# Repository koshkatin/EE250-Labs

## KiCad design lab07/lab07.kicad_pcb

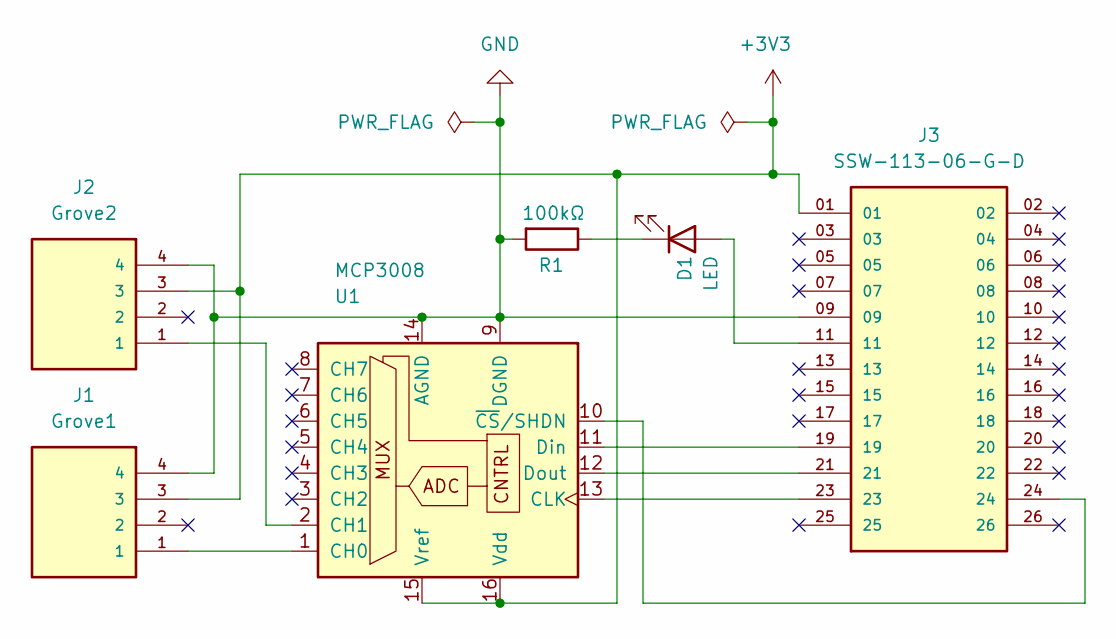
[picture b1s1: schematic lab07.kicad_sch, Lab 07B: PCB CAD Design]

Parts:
D1: LED; LED_D3.0mm
J1: Grove1; SEEED_110990030; PARTREV A
J2: Grove2; SEEED_110990030; PARTREV A
J3: SSW-113-06-G-D; SAMTEC_SSW-113-06-G-D; PARTREV R
R1: 100kΩ; R_Axial_DIN0207_L6.3mm_D2.5mm_P7.62mm_Horizontal
U1: MCP3008; DIP16-2.54-19.2X7.62MM

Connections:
+3V3: J1.3, J2.3, J3.01, U1.15 (Vref), U1.16 (Vdd)
GND: J1.4, J2.4, J3.09, R1.2, U1.9 (DGND), U1.14 (AGND)
unnamed: D1.2 (A), J3.11
unnamed: D1.1 (K), R1.1
unnamed: J1.1, U1.1 (CH0)
unnamed: J2.1, U1.2 (CH1)
unnamed: J3.23, U1.13 (CLK)
unnamed: J3.19, U1.11 (Din)
unnamed: J3.21, U1.12 (Dout)
unnamed: J3.24, U1.10 (~CS/SHDN)

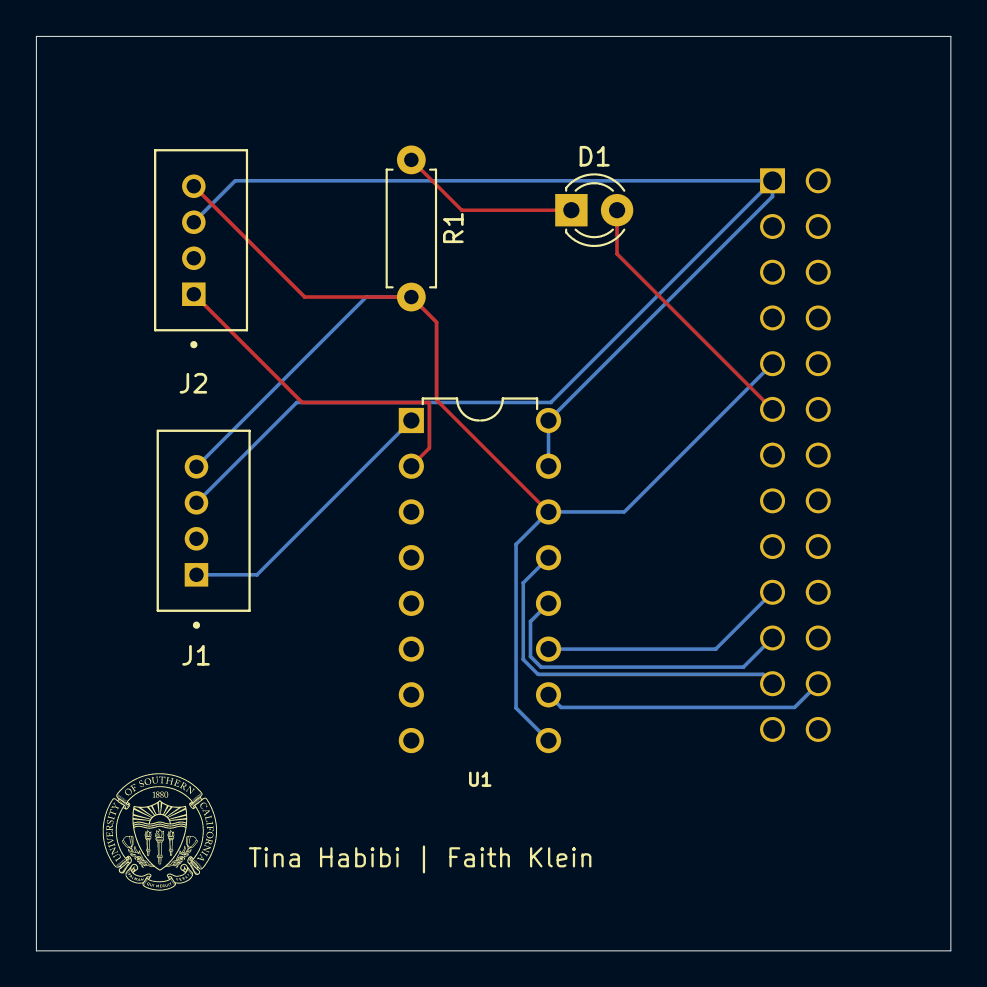
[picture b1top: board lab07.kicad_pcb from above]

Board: 2 copper layers, 50.8 x 50.8 mm, 6 parts (1 on the bottom side), 10 nets.

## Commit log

2025-02-04 Added
2025-02-08 lab3 server.py docstrings
2025-02-17 lab4 added
2025-03-10 New repo
2025-03-11 writeup
2025-03-11 writeup done
2025-03-11 Display on LCD
2025-03-11 Added names
2025-03-11 lab7 test_suite.py ready
2025-03-12 replaced pin
2025-03-31 lab07 and lab08
